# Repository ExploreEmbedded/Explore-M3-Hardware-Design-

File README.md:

# Explore-M3-Hardware-Design-

Explore M3 is a feature rich ARM Cortex M3 development board. It can help you prototype ideas faster with Arduino and take them beyond, with bare metal programming, RTOS support and lower power modes if need be. All the source-code and hardware design files are open-source including the on board boot-loader. This makes it easy in using the board/chip in your custom designs

We are currently crowdfunding the board, click on the link below to support.
https://www.crowdsupply.com/explore-embedded/explore-m3

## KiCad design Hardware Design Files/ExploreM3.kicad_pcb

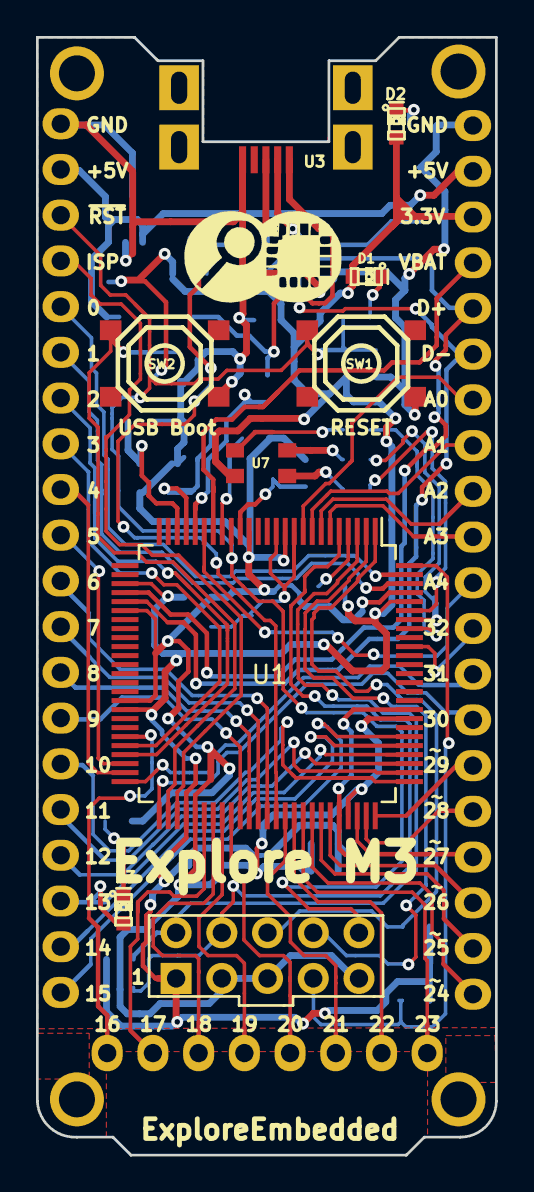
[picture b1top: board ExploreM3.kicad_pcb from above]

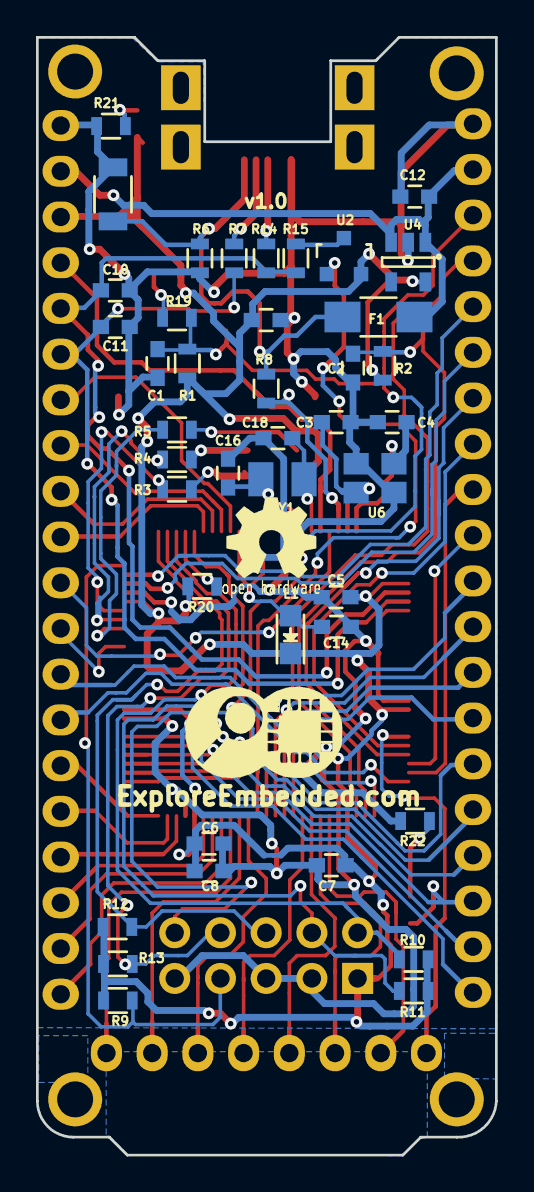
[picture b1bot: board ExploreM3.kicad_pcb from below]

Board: 2 copper layers, 25.5 x 62.1 mm, 66 parts (46 on the bottom side), 73 nets.

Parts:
C1, C2, C5, C6, C7, C8: 0.1uF; C_0603New
C3, C4, C16, C18: 22pf; C_0603New
C9: 100uF, 1206; C_1206
C10, C11: 18pF; C_0603New
C12: 1uF; C_0603New
C14: 0.1uf; C_0603New
C15: 2.2uf; C_0603New
D1, D2, D3: LED; LED-0603_NEW
F1: FUSE; R_1206_HandSoldering
L1: 600E; LED_0805
P1: CONN_02X05; Pin_Header_Straight_2x05
P5, P7: CONN_01X20; Pin_Header_Straight_1x20
P6: GPIO'S; Pin_Header_Straight_1x08
R1, R8, R9, R10, R11, R12, R13, R20: 10K; R_0603_New
R2, R19, R21, R22: 1K; R_0603_New
R3: 150E; R_0603_New
R4, R5: 100E; R_0603_New
R6: 100K; R_0603_New
R7, R14: 33R; R_0603_New
R15: 1.5K; R_0603_New
SW1, SW2: SW_PUSH; smd_push2
U1: LPC1769FBD100; LQFP-100_14x14mm_Pitch0.5mm
U2: BSS84_SOT-23; SOT-23
U3: USB; USB_Micro-B_SMD_NEW
U4: AP2112K; SOT-23-5
U5, U8: EE_Logo; Logo_8
U6: 12Mhz_SMD; 12Mhz_SMD_4pin
U7: RGB_4pin; RGB_SMD_4pin_New
U9, U10, U11, U12: MountingHole; 1pin
U13: OSH_Symbol; Logo_silk_OSHW_6x6mm
U14, U15, U16, U17, U18, U19: PWM_Symbol; pwm
Y1: RTC Crystal; SMD_RTC_Crstl

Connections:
+3V3: C5.1, C6.1, C7.1, C8.1, C15.1, D1.1, D2.1, L1.1, P1.1, P7.3, R1.1, R2.1, R9.2, R10.1, R11.1, R12.1, R13.1, R20.1, U1.28, U1.42, U1.54, U1.71, U1.84, U1.96, U2.2, U4.5, U7.1
+5V: C12.1, F1.1, P5.2, P7.2, U4.1, U4.3
/ISP: P5.4, U1.53
/LED_B: R5.1, U1.93
/LED_G: R4.1, U1.94
/LED_R: R3.1, U1.95
/P0_0: P5.8, U1.46
/P0_1: P5.7, U1.47
/P0_2: P5.6, U1.98
/P0_3: P5.5, U1.99
/P0_4: P5.20, U1.81
/P0_5: P5.19, U1.80
/P0_6: D3.1, P5.18, U1.79
/P0_7: P5.17, U1.78
/P0_8: P5.16, U1.77
/P0_9: P5.15, U1.76
/P0_10: P5.10, U1.48
/P0_11: P5.9, U1.49
/P0_15: P5.12, U1.62
/P0_16: P5.11, U1.63
/P0_17: P5.13, U1.61
/P0_18: P5.14, U1.60
/P0_19: P6.4, U1.59
/P0_20: P6.5, U1.58
/P0_21: P6.6, U1.57
/P0_22: P6.7, U1.56
/P0_23: P7.7, U1.9
/P0_24: P7.8, U1.8
/P0_25: P7.9, U1.7
/P0_26: P7.10, U1.6
/P1_9: P7.12, U1.91
/P1_29: P6.8, U1.45
/P1_31: P7.11, U1.20
/P2_0: P7.15, U1.75
/P2_1: P7.16, U1.74
/P2_2: P7.17, U1.73
/P2_3: P7.18, U1.70
/P2_4: P7.19, U1.69
/P2_5: P7.20, U1.68
/P2_6: P6.1, U1.67
/P2_7: P6.2, U1.66
/P2_8: P6.3, U1.65
/P2_12: P7.14, U1.51
/P2_13: P7.13, U1.50
/RTCK: P1.7, R9.1, U1.100
/TCK/SWDCLK: P1.4, R11.2, U1.5
/TDI: P1.8, R13.2, U1.2
/TDO/SWD: P1.6, R12.2, U1.1
/TMS/SWDIO: P1.2, R10.2, U1.3
/USB_BOOT: C2.1, R2.2, SW2.1, U1.52
/USB_CONNECT: U1.64, U2.1
/USB_D+: C10.1, P7.5, R14.1, R15.2, U1.29
/USB_D-: C11.1, P7.6, R7.1, U1.30
/VBAT: P7.4, U1.19
/VBUS: R8.2, U1.21
/VDDA: C14.2, L1.2, U1.10, U1.12
/~RST: C1.1, P1.10, P5.3, R1.2, R19.2, SW1.1, U1.17
GND: C1.2, C2.2, C3.1, C4.2, C5.2, C6.2, C7.2, C8.2, C9.2, C10.2, C11.2, C12.2, C14.1, C15.2, C16.2, C18.2, P1.3, P1.5, P1.9, P5.1, P7.1, R6.1, R21.2, R22.2, SW1.2, SW2.2, U1.11, U1.15, U1.31, U1.41, U1.55, U1.72, U1.83, U1.97, U3.5, U4.2, U6.2, U6.4
unnamed: C3.2, U1.22, U6.1
unnamed: C4.1, U1.23, U6.3
unnamed: C9.1, F1.2, R6.2, R8.1, U3.1
unnamed: C16.1, U1.16, Y1.1
unnamed: C18.1, U1.18, Y1.2
unnamed: D1.2, R19.1
unnamed: D2.2, R21.1
unnamed: D3.2, R22.1
unnamed: R3.2, U7.2
unnamed: R4.2, U7.4
unnamed: R5.2, U7.3
unnamed: R7.2, U3.2
unnamed: R14.2, U3.3
unnamed: R15.1, U2.3
unnamed: R20.2, U1.4

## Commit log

2016-09-09 Design Files
2016-09-20 Added filled zones
2016-10-08 Moved LED
2016-10-10 Version name modified on Silkscreen
2017-03-20 BOM added
2018-05-11 Revised BOM
2018-05-12 Boards are arranged in the Panel
2018-06-07 Board Test code added
    1. Footprint labels added
    2. Board Test coded added
